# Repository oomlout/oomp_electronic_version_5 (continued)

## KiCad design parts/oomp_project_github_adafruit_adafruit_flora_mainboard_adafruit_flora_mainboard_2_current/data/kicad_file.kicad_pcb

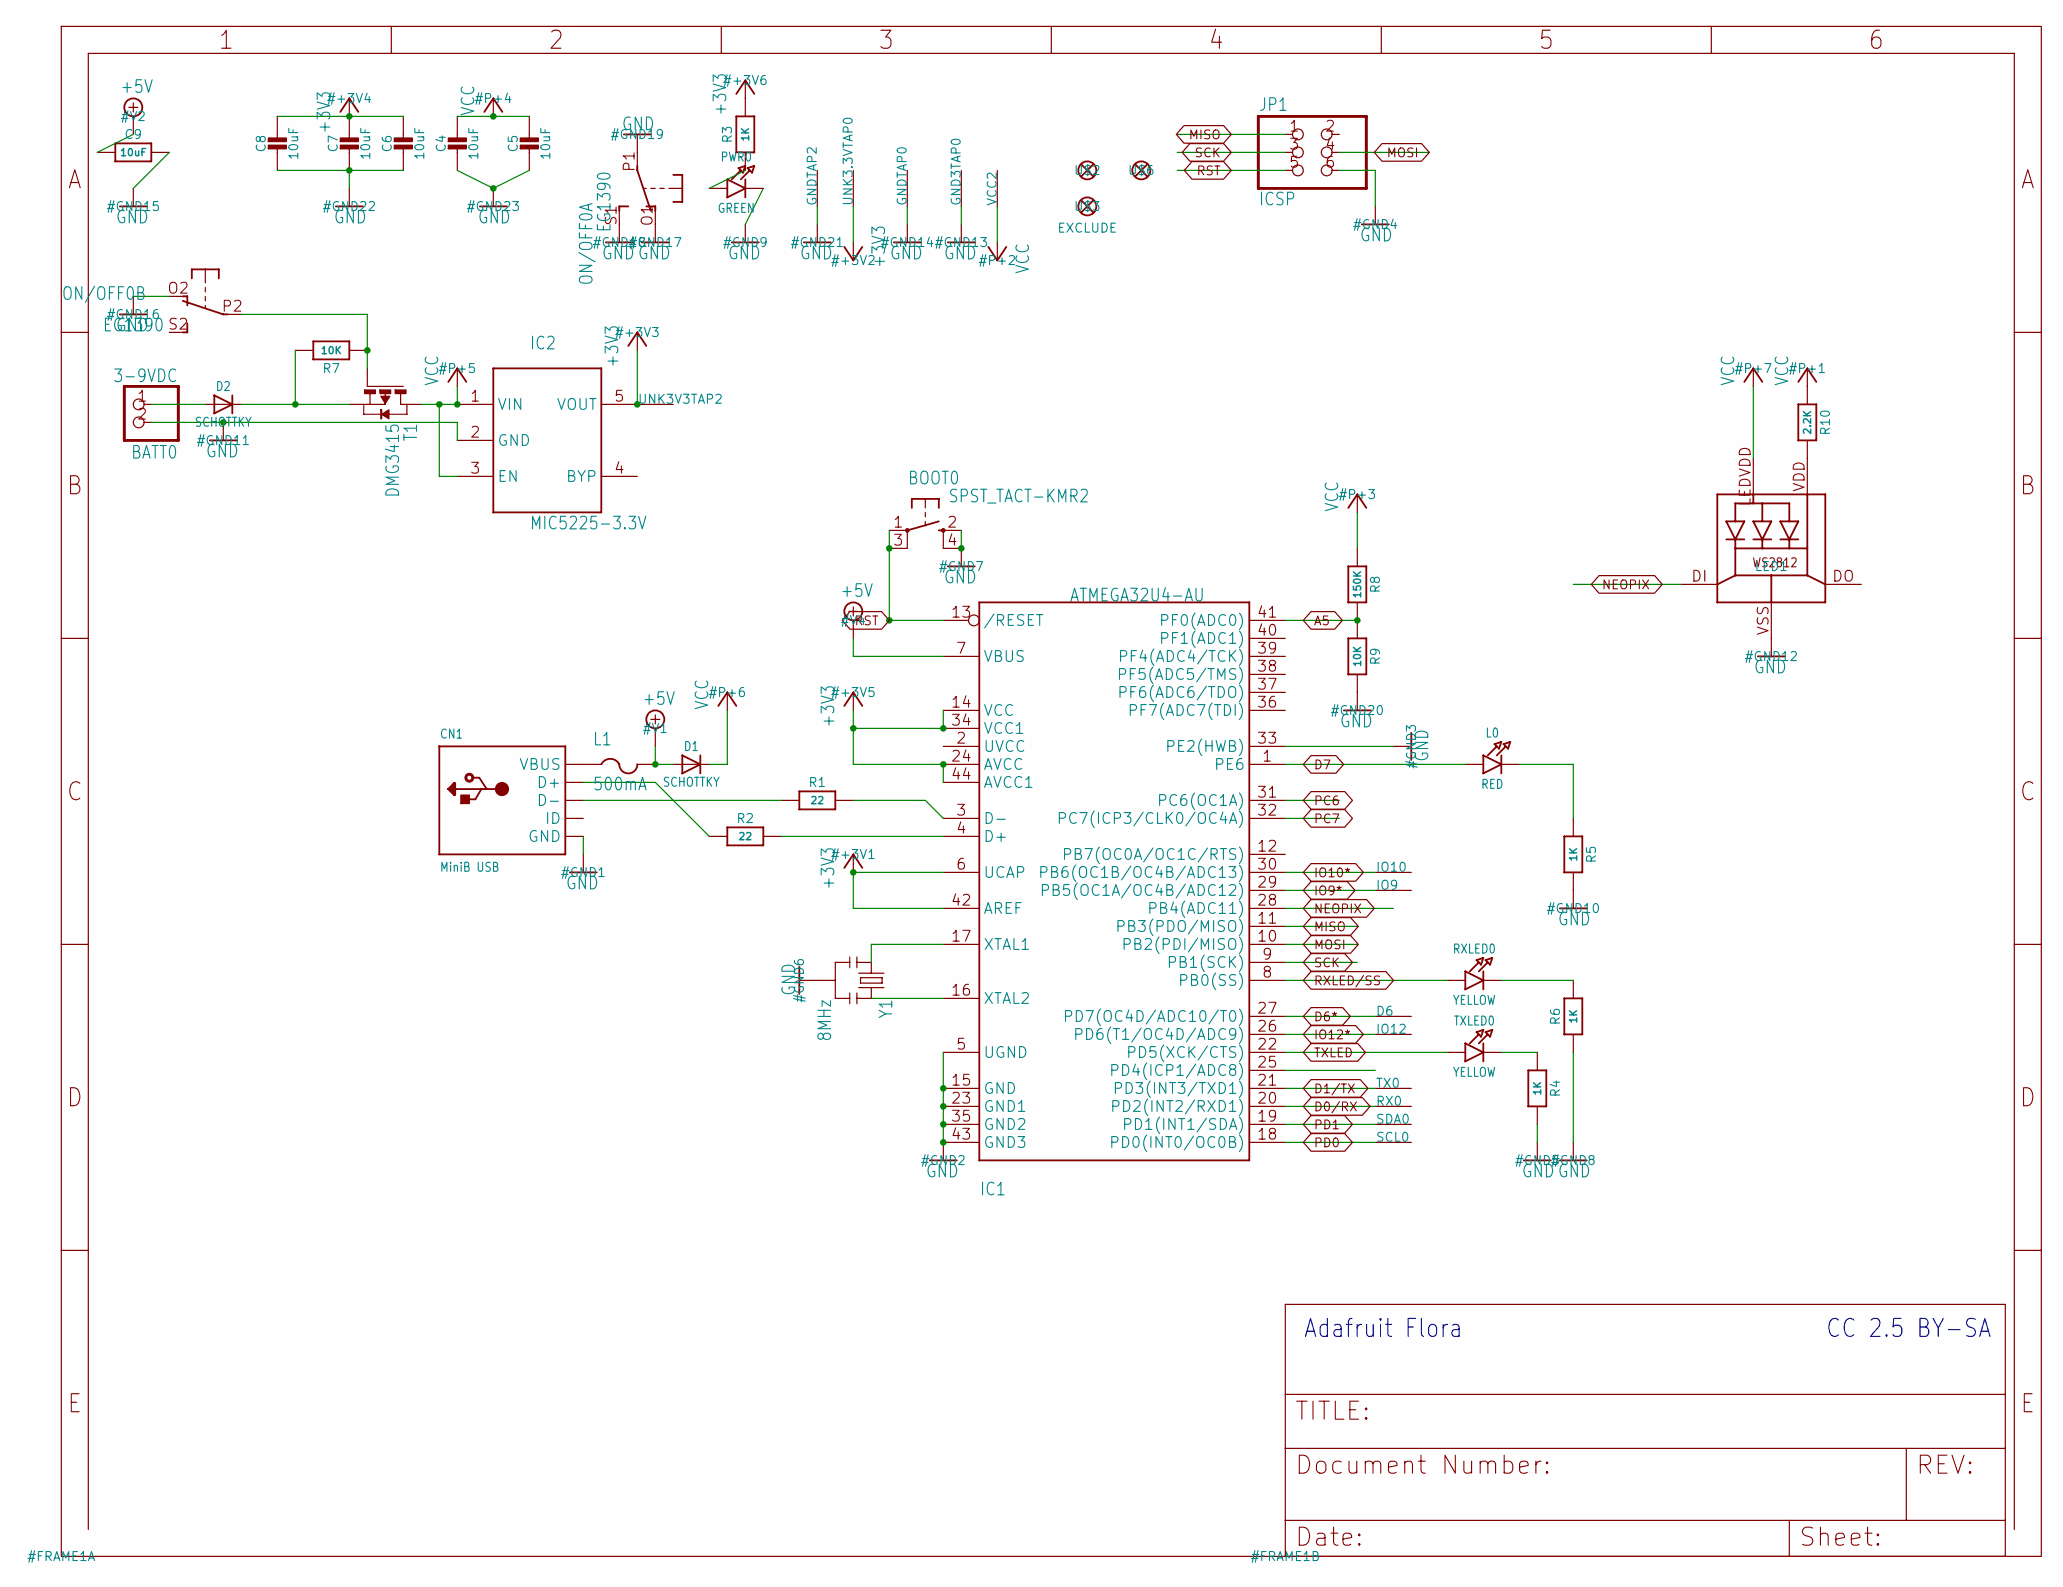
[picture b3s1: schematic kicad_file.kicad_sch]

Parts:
BATT0: 3-9VDC; JST-PH-2-SMT-RA
BOOT0: SPST_TACT-KMR2; KMR2
C4, C5, C6, C7, C8: 10uF; 0805-NO
C9: 10uF; _0805MP
CN1: MiniB USB; 4UCONN_20329
D1, D2: SCHOTTKY; SOD-123
D6: SEWTAP-2.0IN; SEWINGTAP_2.0
GND3TAP0: SEWTAP-2.0IN; SEWINGTAP_2.0
GNDTAP0, GNDTAP2: SEWTAP-2.0IN; SEWINGTAP_2.0
IC1: ATMEGA32U4-AU; TQFP44
IC2: MIC5225-3.3V; SOT23-5L
IO9, IO10, IO12: SEWTAP-2.0IN; SEWINGTAP_2.0
JP1: ICSP; 2X03
L0: RED; CHIPLED_0805_NOOUTLINE
L1: 500mA; R1206
LED1: WS2812
ON/OFF0: EG1390
PWR0: GREEN; CHIPLED_0805_NOOUTLINE
R1, R2: 22; 0805-NO
R3, R4: 1K; _0805MP
R5, R6: 1K; 0805-NO
R7: 10K; _0805MP
R8: 150K; 0805-NO
R9: 10K; 0805-NO
R10: 2.2K; 0805-NO
RX0: SEWTAP-2.0IN; SEWINGTAP_2.0
RXLED0: YELLOW; CHIPLED_0805_NOOUTLINE
SCL0: SEWTAP-2.0IN; SEWINGTAP_2.0
SDA0: SEWTAP-2.0IN; SEWINGTAP_2.0
T1: DMG3415; SOT-23
TX0: SEWTAP-2.0IN; SEWINGTAP_2.0
TXLED0: YELLOW; CHIPLED_0805_NOOUTLINE
U$2, U$3, U$6: FIDUCIAL""; FIDUCIAL_1MM
UNK3.3VTAP0, UNK3V3TAP2: SEWTAP-2.0IN; SEWINGTAP_2.0
VCC2: SEWTAP-2.0IN; SEWINGTAP_2.0
Y1: 8MHz; RESONATOR-SMD

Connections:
+3V3: C6.1, C7.1, C8.1, IC1.6 (UCAP), IC1.14 (VCC), IC1.24 (AVCC), IC1.34 (VCC1), IC1.42 (AREF), IC1.44 (AVCC1), IC2.5 (VOUT), R3.2, UNK3.3VTAP0.P$1, UNK3V3TAP2.P$1
+5V: C9.1, D1.A, IC1.7 (VBUS), L1.2
A5: IC1.41 (PF0(ADC0)), R8.2, R9.1
D0/RX: IC1.20 (PD2(INT2/RXD1)), RX0.P$1
D1/TX: IC1.21 (PD3(INT3/TXD1)), TX0.P$1
D6*: D6.P$1, IC1.27 (PD7(OC4D/ADC10/T0))
D7: IC1.1 (PE6), L0.A
GND: BATT0.2 (1), BOOT0.2 (S), BOOT0.4 (S1), C4.2, C5.2, C6.2, C7.2, C8.2, C9.2, CN1.BASE@1 (GND), CN1.BASE@2 (GND), CN1.GND, CN1.SPRT@1 (GND), CN1.SPRT@2 (GND), CN1.SPRT@3 (GND), CN1.SPRT@4 (GND), GND3TAP0.P$1, GNDTAP0.P$1, GNDTAP2.P$1, IC1.5 (UGND), IC1.15 (GND), IC1.23 (GND1), IC1.33 (PE2(HWB)), IC1.35 (GND2), IC1.43 (GND3), IC2.2 (GND), JP1.6, LED1.VSS (GND), ON/OFF0.O1 (O), ON/OFF0.O2 (O), ON/OFF0.P1, ON/OFF0.S1 (S), PWR0.C, R4.2, R5.2, R6.1, R9.2, Y1.2
IO9*: IC1.29 (PB5(OC1A/OC4B/ADC12)), IO9.P$1
IO10*: IC1.30 (PB6(OC1B/OC4B/ADC13)), IO10.P$1
IO12*: IC1.26 (PD6(T1/OC4D/ADC9)), IO12.P$1
MISO: IC1.11 (PB3(PDO/MISO)), JP1.1
MOSI: IC1.10 (PB2(PDI/MISO)), JP1.4
unnamed: PWR0.A, R3.1
unnamed: CN1.D+, R2.1
unnamed: IC1.3 (D-), R1.2
unnamed: IC1.4 (D+), R2.2
unnamed: CN1.D-, R1.1
unnamed: D2.C, R7.2, T1.2 (S)
unnamed: BATT0.1 (2), D2.A
unnamed: IC1.17 (XTAL1), Y1.1
unnamed: IC1.16 (XTAL2), Y1.3
unnamed: L0.C, R5.1
unnamed: R4.1, TXLED0.C
unnamed: R6.2, RXLED0.C
unnamed: ON/OFF0.P2, R7.1, T1.3 (G)
unnamed: LED1.VDD, R10.2
NEOPIX: IC1.28 (PB4(ADC11)), LED1.DI
PC6: IC1.31 (PC6(OC1A))
PC7: IC1.32 (PC7(ICP3/CLK0/OC4A))
PD0: IC1.18 (PD0(INT0/OC0B)), SCL0.P$1
PD1: IC1.19 (PD1(INT1/SDA)), SDA0.P$1
RST: BOOT0.1, BOOT0.3 (P1), IC1.13 (/RESET), JP1.5
RXLED/SS: IC1.8 (PB0(SS)), RXLED0.A
SCK: IC1.9 (PB1(SCK)), JP1.3
TXLED: IC1.22 (PD5(XCK/CTS)), TXLED0.A
VBUS: CN1.VBUS, L1.1
VCC: C4.1, C5.1, D1.C, IC2.1 (VIN), IC2.3 (EN), LED1.LEDVDD, R8.1, R10.1, T1.1 (D), VCC2.P$1

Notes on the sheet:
CC 2.5 BY-SA
Adafruit Flora

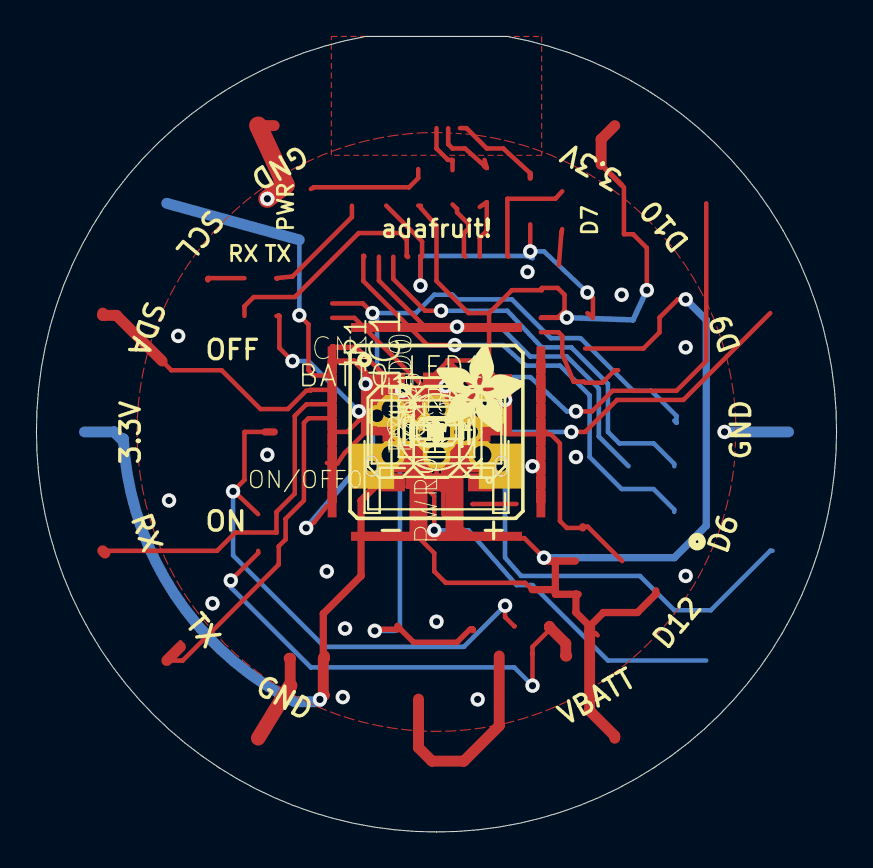
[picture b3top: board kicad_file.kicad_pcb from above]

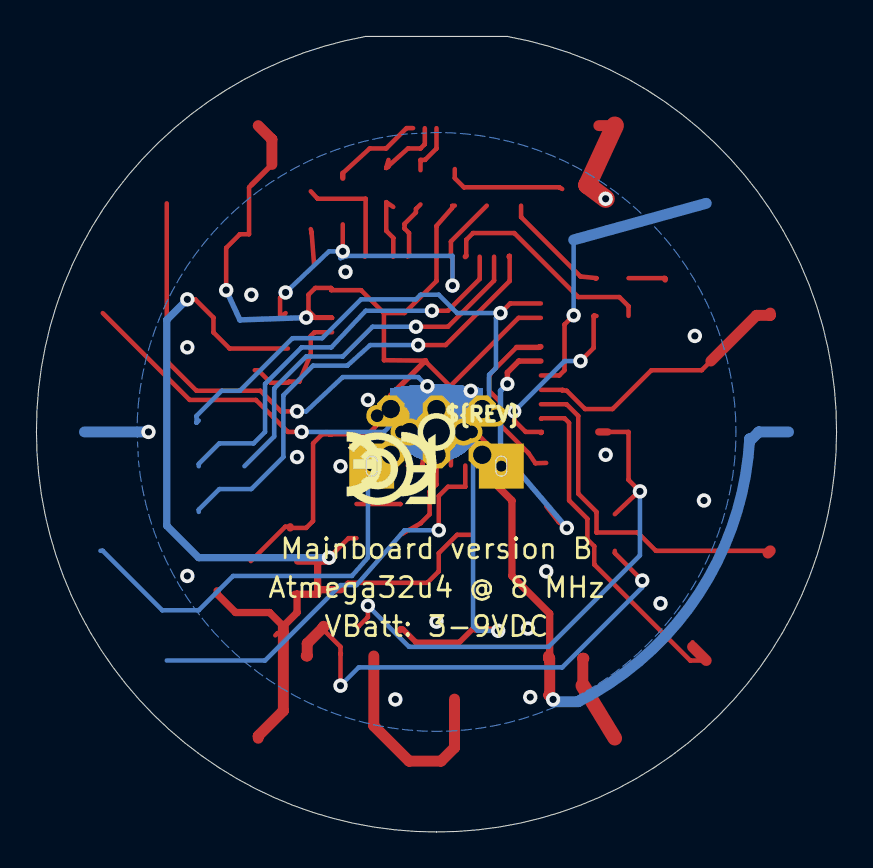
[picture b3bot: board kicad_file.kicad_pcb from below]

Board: 16 copper layers, 44.5 x 44.2 mm, 55 parts (4 on the bottom side), 36 nets.

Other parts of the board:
U$1: ADAFRUIT_5MM
U$4: FLORAMED
U$5: PCBFEAT-REV-040
U$7: SYMBOL_FCC_5MM
U$8: SYMBOL_CE_5MM

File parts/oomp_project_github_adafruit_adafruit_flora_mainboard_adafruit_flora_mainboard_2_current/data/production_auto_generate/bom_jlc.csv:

Comment,Designator,Footprint,LCSC Part #
,U$1,adafruit flora mainboard 2-import-fps:ADAFRUIT_5MM,
,U$4,adafruit flora mainboard 2-import-fps:FLORAMED,
,U$5,adafruit flora mainboard 2-import-fps:PCBFEAT-REV-040,
,U$8,adafruit flora mainboard 2-import-fps:SYMBOL_CE_5MM,
,U$7,adafruit flora mainboard 2-import-fps:SYMBOL_FCC_5MM,
10K,R9,adafruit flora mainboard 2-import-fps:0805-NO,C17414
10K,R7,adafruit flora mainboard 2-import-fps:_0805MP,C17414
10uF,"C4,C5,C6,C7,C8",adafruit flora mainboard 2-import-fps:0805-NO,
10uF,C9,adafruit flora mainboard 2-import-fps:_0805MP,
150K,R8,adafruit flora mainboard 2-import-fps:0805-NO,C2907228
1K,"R5,R6",adafruit flora mainboard 2-import-fps:0805-NO,C17513
1K,"R3,R4",adafruit flora mainboard 2-import-fps:_0805MP,C17513
2.2K,R10,adafruit flora mainboard 2-import-fps:0805-NO,C17520
22,"R1,R2",adafruit flora mainboard 2-import-fps:0805-NO,C2907310
3-9VDC,BATT0,adafruit flora mainboard 2-import-fps:JST-PH-2-SMT-RA,
500mA,L1,adafruit flora mainboard 2-import-fps:R1206,
8MHz,Y1,adafruit flora mainboard 2-import-fps:RESONATOR-SMD,
ATMEGA32U4-AU,IC1,adafruit flora mainboard 2-import-fps:TQFP44,
DMG3415,T1,adafruit flora mainboard 2-import-fps:SOT-23,
EG1390,ON/OFF0,adafruit flora mainboard 2-import-fps:EG1390,
"FIDUCIAL""""","U$2,U$3,U$6",adafruit flora mainboard 2-import-fps:FIDUCIAL_1MM,
GREEN,PWR0,adafruit flora mainboard 2-import-fps:CHIPLED_0805_NOOUTLINE,
ICSP,JP1,adafruit flora mainboard 2-import-fps:2X03,
MIC5225-3.3V,IC2,adafruit flora mainboard 2-import-fps:SOT23-5L,
MiniB USB,CN1,adafruit flora mainboard 2-import-fps:4UCONN_20329,
RED,L0,adafruit flora mainboard 2-import-fps:CHIPLED_0805_NOOUTLINE,
SCHOTTKY,"D1,D2",adafruit flora mainboard 2-import-fps:SOD-123,
SPST_TACT-KMR2,BOOT0,adafruit flora mainboard 2-import-fps:KMR2,
WS2812,LED1,adafruit flora mainboard 2-import-fps:WS2812,
YELLOW,"RXLED0,TXLED0",adafruit flora mainboard 2-import-fps:CHIPLED_0805_NOOUTLINE,

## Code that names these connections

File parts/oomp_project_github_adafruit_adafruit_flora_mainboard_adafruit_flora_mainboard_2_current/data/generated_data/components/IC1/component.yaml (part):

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    dnp: false
    pins:
    - number: '1'
      name: PE6
      electrical_type: bidirectional
      graphic_style: line
      local_position:
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        pin_name: VCC
      - reference: IC1
        pin_number: '24'
        pin_name: AVCC
      - reference: IC1
        pin_number: '34'
        pin_name: VCC1
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        pin_number: '2'
        pin_name: '2'
    - number: '8'
      name: PB0(SS)
      electrical_type: bidirectional
      graphic_style: line
      local_position:
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        pin_number: A
        pin_name: A
    - number: '9'
      name: PB1(SCK)
      electrical_type: bidirectional
      graphic_style: line
      local_position:
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        pin_number: '3'
        pin_name: '3'
    - number: '10'
      name: PB2(PDI/MISO)
      electrical_type: bidirectional
      graphic_style: line
      local_position:
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        pin_number: '4'
        pin_name: '4'
    - number: '11'
      name: PB3(PDO/MISO)
      electrical_type: bidirectional
      graphic_style: line
      local_position:
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        pin_number: '1'
        pin_name: '1'
    - number: '12'
      name: PB7(OC0A/OC1C/RTS)
      electrical_type: bidirectional
      graphic_style: line
      local_position:
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        pin_name: UCAP
      - reference: IC1
        pin_number: '24'
        pin_name: AVCC
      - reference: IC1
        pin_number: '34'
        pin_name: VCC1
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        pin_number: '1'
        pin_name: '1'
    - number: '18'
      name: PD0(INT0/OC0B)
      electrical_type: bidirectional
      graphic_style: line
      local_position:
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      position:
        x: 195.58
        y: 175.26
      net: PD0
      net_aliases:
      - PD0
      net_scope: global
      no_connect: false
      connected_to:
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        pin_number: P$1
        pin_name: SEW
    - number: '19'
      name: PD1(INT1/SDA)
      electrical_type: bidirectional
      graphic_style: line
      local_position:
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      position:
        x: 195.58
        y: 172.72
      net: PD1
      net_aliases:
      - PD1
      net_scope: global
      no_connect: false
      connected_to:
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        pin_number: P$1
        pin_name: SEW
    - number: '20'
      name: PD2(INT2/RXD1)
      electrical_type: bidirectional
      graphic_style: line
      local_position:
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        pin_number: P$1
        pin_name: SEW
    - number: '21'
      name: PD3(INT3/TXD1)
      electrical_type: bidirectional
      graphic_style: line
      local_position:
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        pin_number: P$1
        pin_name: SEW
    - number: '22'
      name: PD5(XCK/CTS)
      electrical_type: bidirectional
      graphic_style: line
      local_position:
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      no_connect: false
      connected_to: []
    - number: '26'
      name: PD6(T1/OC4D/ADC9)
      electrical_type: bidirectional
      graphic_style: line
      local_position:
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        pin_number: P$1
        pin_name: SEW
    - number: '27'
      name: PD7(OC4D/ADC10/T0)
      electrical_type: bidirectional
      graphic_style: line
      local_position:
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        pin_number: P$1
        pin_name: SEW
    - number: '28'
      name: PB4(ADC11)
      electrical_type: bidirectional
      graphic_style: line
      local_position:
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        pin_number: DI
        pin_name: DI
    - number: '29'
      name: PB5(OC1A/OC4B/ADC12)
      electrical_type: bidirectional
      graphic_style: line
      local_position:
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        pin_number: P$1
        pin_name: SEW
    - number: '30'
      name: PB6(OC1B/OC4B/ADC13)
      electrical_type: bidirectional
      graphic_style: line
      local_position:
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        pin_number: P$1
        pin_name: SEW
    - number: '31'
      name: PC6(OC1A)
      electrical_type: bidirectional
      graphic_style: line
      local_position:
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      position:
        x: 195.58
        y: 127.0
      net: PC6
      net_aliases:
      - PC6
      net_scope: global
      no_connect: false
      connected_to: []
    - number: '32'
      name: PC7(ICP3/CLK0/OC4A)
      electrical_type: bidirectional
      graphic_style: line
      local_position:
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      position:
        x: 195.58
        y: 129.54
      net: PC7
      net_aliases:
      - PC7
      net_scope: global
      no_connect: false
      connected_to: []
    - number: '33'
      name: PE2(HWB)
      electrical_type: bidirectional
      graphic_style: line
      local_position:
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        pin_name: VCC
      - reference: IC1
        pin_number: '24'
        pin_name: AVCC
      - reference: IC1
        pin_number: '42'
        pin_name: AREF
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      no_connect: false
      connected_to: []
    - number: '41'
      name: PF0(ADC0)
      electrical_type: bidirectional
      graphic_style: line
      local_position:
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        pin_name: VCC
      - reference: IC1
        pin_number: '24'
        pin_name: AVCC
      - reference: IC1
        pin_number: '34'
        pin_name: VCC1
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        pin_name: VCC
      - reference: IC1
        pin_number: '24'
        pin_name: AVCC
      - reference: IC1
        pin_number: '34'
        pin_name: VCC1
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    pin_name: GND1
  - reference: IC1
    pin_number: '24'
    pin_name: AVCC
  - reference: IC1
    pin_number: '34'
    pin_name: VCC1
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    - F.Cu
    - F.Mask
    - F.Paste
    net: PD0
    net_number: null
    pin_function: null
    pin_type: null
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    - F.Cu
    - F.Mask
    - F.Paste
    net: PD1
    net_number: null
    pin_function: null
    pin_type: null
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    - F.Cu
    - F.Mask
    - F.Paste
    net: PC6
    net_number: null
    pin_function: null
    pin_type: null
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    - F.Cu
    - F.Mask
    - F.Paste
    net: PC7
    net_number: null
    pin_function: null
    pin_type: null
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    status: incomplete
  - pin_or_pad_number: '18'
    schematic_nets:
    - PD0
    pcb_nets:
    - PD0
    status: agree
  - pin_or_pad_number: '19'
    schematic_nets:
    - PD1
    pcb_nets:
    - PD1
    status: agree
  - pin_or_pad_number: '2'
    schematic_nets: []
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    status: agree
  - pin_or_pad_number: '31'
    schematic_nets:
    - PC6
    pcb_nets:
    - PC6
    status: agree
  - pin_or_pad_number: '32'
    schematic_nets:
    - PC7
    pcb_nets:
    - PC7
    status: agree
  - pin_or_pad_number: '33'
    schematic_nets: []
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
